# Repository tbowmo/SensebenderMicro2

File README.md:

## Sensebender Micro v2

Revamped Sensebender Micro, with Atmel SAMD20 processor instead of atmega 328p.

Enhancements over old Sensebender:

- up to 256Kb flash/32Kb RAM for code
- up to 48Mhz operating freq.
- 2 LEDs
- Dual radio
  - RFM69
  - NRF24 mini / smd
- onboard voltage regulator, can be disabled / bypassed with solderbridges
- Temperature / Humidity sensor Si7021
- Onboard external flash for future OTA (bootloader is not developed yet)
- Use [MYSX2.4](https://www.mysensors.org/hardware/mysx#mysx-24) connector for add-on boards

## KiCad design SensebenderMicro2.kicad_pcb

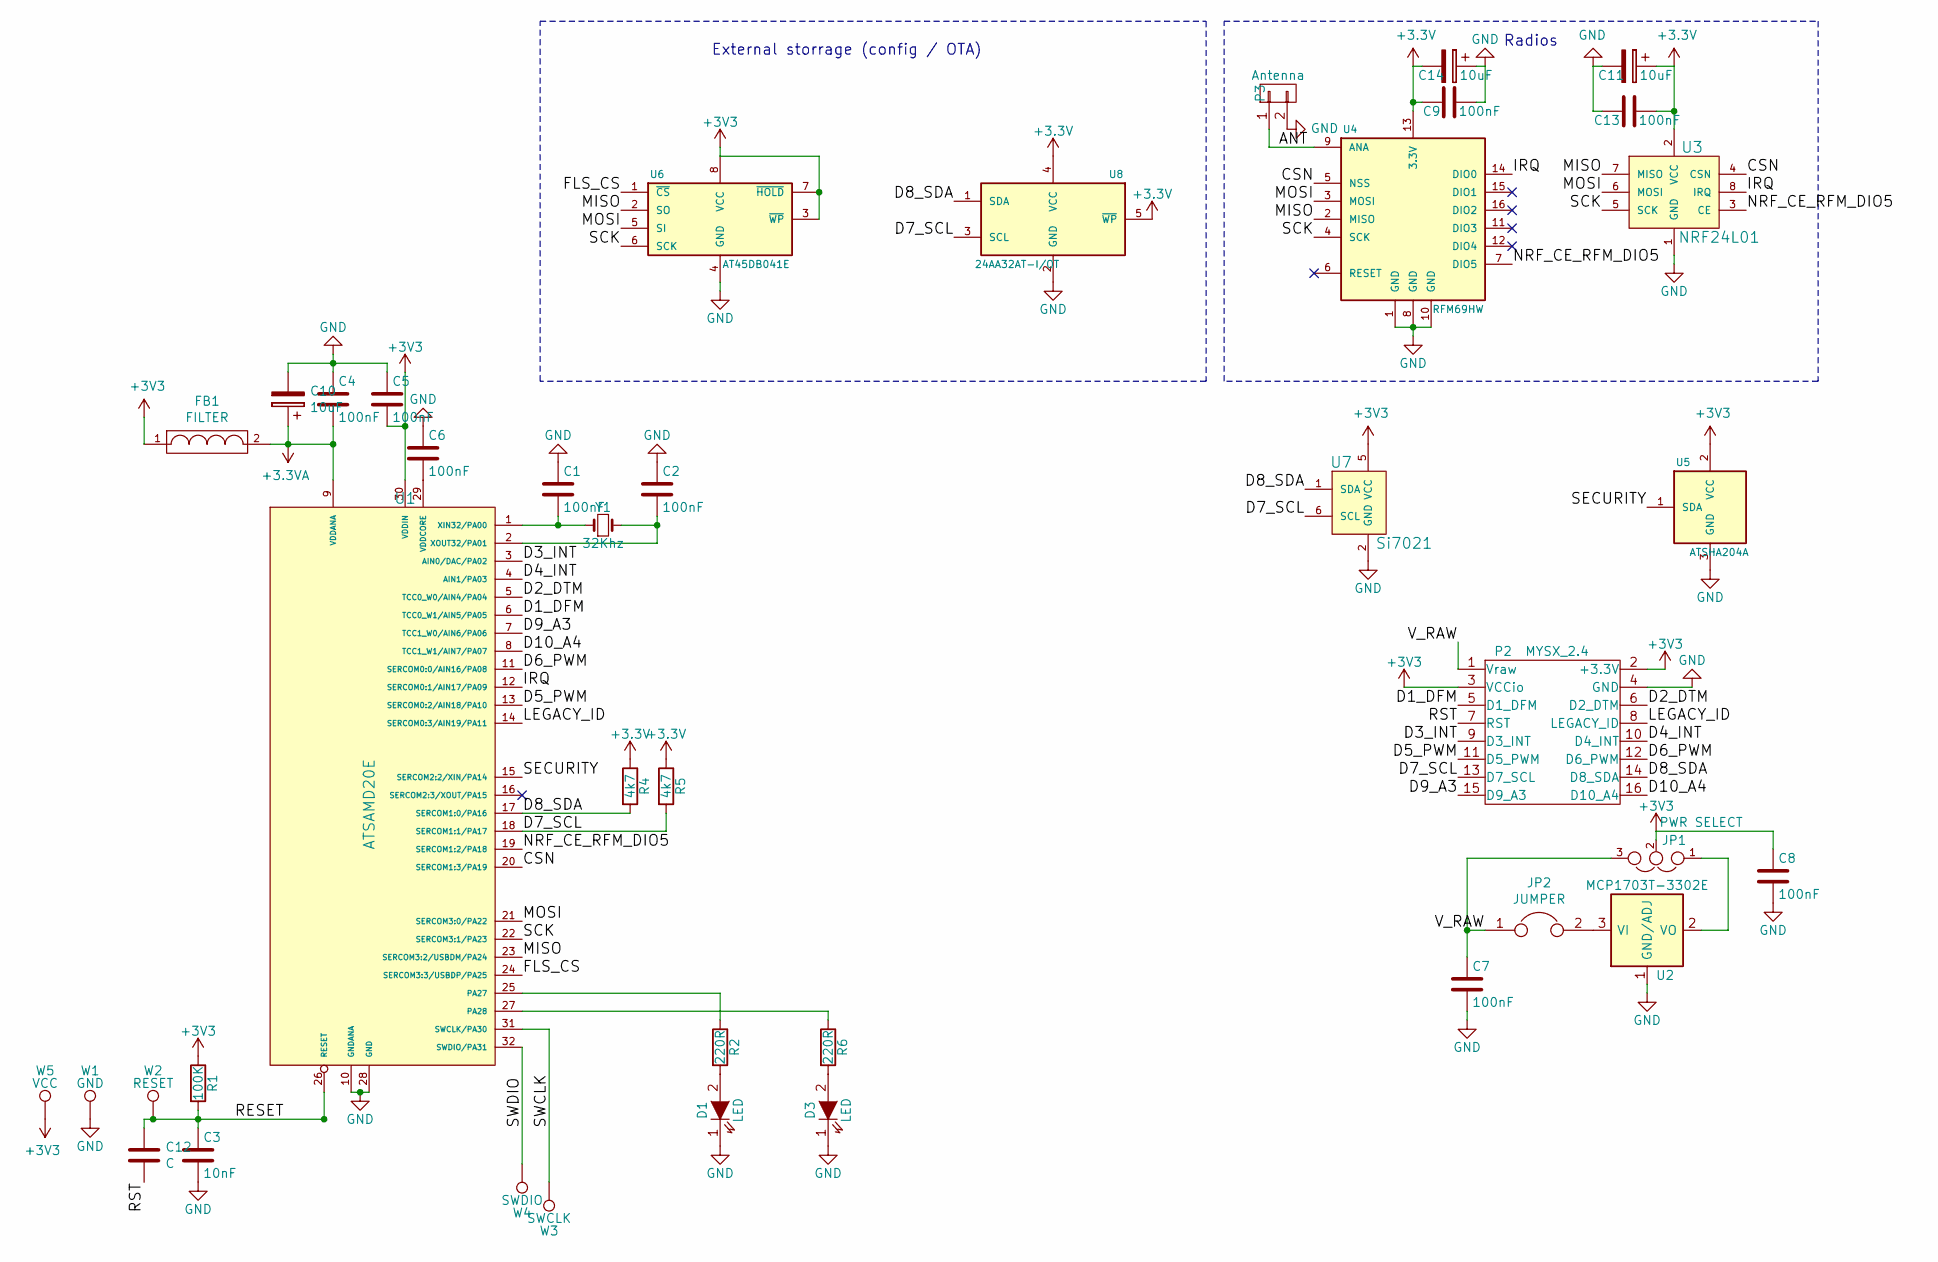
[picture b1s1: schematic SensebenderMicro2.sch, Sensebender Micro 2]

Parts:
C1, C2, C4, C5, C6, C7, C8, C9, C13: 100nF; C_0603
C3: 10nF; C_0603
C10, C11, C14: 10uF; C_0603
C12: C; C_0603
D1, D3: LED; LED-0603
FB1: FILTER; R_0603
JP1: PWR SELECT; 3_pin_solder_jumper_smd
JP2: JUMPER; 2_pin_solder_jumper_smd
P2: MYSX_2.4; MYSX_1.3
P3: Antenna; Pin_Header_Angled_1x02
R1: 100K; R_0603
R2, R6: 220R; R_0603
R4, R5: 4k7; R_0603
U1: ATSAMD20E; TQFP-32_7x7mm_Pitch0.8mm
U2: MCP1703T-3302E; SOT-23
U3: NRF24L01; NRF24L01-SMD
U4: RFM69HW; RFM69HW_SMD_Handsoldering
U5: ATSHA204A; SOT-23_Handsoldering
U6: AT45DB041E; SOIC-8_3.9x4.9mm_Pitch1.27mm
U7: Si7021; DFN-6-1EP_3x3mm_Pitch0.95mm
U8: 24AA32AT-I/OT; SOT-23-5
W1: GND; Measurement_Point_Round-SMD-Pad_Small
W2: RESET; Measurement_Point_Round-SMD-Pad_Small
W3: SWCLK; Measurement_Point_Round-SMD-Pad_Small
W4: SWDIO; Measurement_Point_Round-SMD-Pad_Small
W5: VCC; Measurement_Point_Round-SMD-Pad_Small
Y1: 32Khz; XTAL_3.2x1.5mm

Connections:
+3.3VA: C4.2, C10.1, FB1.2, U1.9 (VDDANA)
/ANT: P3.1, U4.9 (ANA)
/CSN: U1.20 (SERCOM1:3/PA19), U3.4 (CSN), U4.5 (NSS)
/D1_DFM: P2.5 (D1_DFM), U1.6 (TCC0_W1/AIN5/PA05)
/D2_DTM: P2.6 (D2_DTM), U1.5 (TCC0_W0/AIN4/PA04)
/D3_INT: P2.9 (D3_INT), U1.3 (AIN0/DAC/PA02)
/D4_INT: P2.10 (D4_INT), U1.4 (AIN1/PA03)
/D5_PWM: P2.11 (D5_PWM), U1.13 (SERCOM0:2/AIN18/PA10)
/D6_PWM: P2.12 (D6_PWM), U1.11 (SERCOM0:0/AIN16/PA08)
/D7_SCL: P2.13 (D7_SCL), R5.2, U1.18 (SERCOM1:1/PA17), U7.6 (SCL), U8.3 (SCL)
/D8_SDA: P2.14 (D8_SDA), R4.2, U1.17 (SERCOM1:0/PA16), U7.1 (SDA), U8.1 (SDA)
/D9_A3: P2.15 (D9_A3), U1.7 (TCC1_W0/AIN6/PA06)
/D10_A4: P2.16 (D10_A4), U1.8 (TCC1_W1/AIN7/PA07)
/FLS_CS: U1.24 (SERCOM3:3/USBDP/PA25), U6.1 (~CS)
/IRQ: U1.12 (SERCOM0:1/AIN17/PA09), U3.8 (IRQ), U4.14 (DIO0)
/LEGACY_ID: P2.8 (LEGACY_ID), U1.14 (SERCOM0:3/AIN19/PA11)
/MISO: U1.23 (SERCOM3:2/USBDM/PA24), U3.7 (MISO), U4.2 (MISO), U6.2 (SO)
/MOSI: U1.21 (SERCOM3:0/PA22), U3.6 (MOSI), U4.3 (MOSI), U6.5 (SI)
/NRF_CE_RFM_DIO5: U1.19 (SERCOM1:2/PA18), U3.3 (CE), U4.7 (DIO5)
/RESET: C3.1, C12.1, R1.2, U1.26 (RESET), W2.1
/RST: C12.2, P2.7 (RST)
/SCK: U1.22 (SERCOM3:1/PA23), U3.5 (SCK), U4.4 (SCK), U6.6 (SCK)
/SECURITY: U1.15 (SERCOM2:2/XIN/PA14), U5.1 (SDA)
/SWCLK: U1.31 (SWCLK/PA30), W3.1
/SWDIO: U1.32 (SWDIO/PA31), W4.1
/V_RAW: C7.1, JP1.3, JP2.1, P2.1 (Vraw)
GND: C1.1, C2.1, C3.2, C4.1, C5.1, C6.1, C7.2, C8.2, C9.1, C10.2, C11.2, C13.2, C14.1, D1.1 (K), D3.1 (K), P2.4 (GND), P3.2, U1.10 (GNDANA), U1.28 (GND), U2.1 (GND/ADJ), U3.1 (GND), U4.1 (GND), U4.8 (GND), U4.10 (GND), U5.3 (GND), U6.4 (GND), U7.2 (GND), U8.2 (GND), W1.1
unnamed: C1.2, U1.1 (XIN32/PA00), Y1.1
unnamed: C2.2, U1.2 (XOUT32/PA01), Y1.2
unnamed: C6.2, U1.29 (VDDCORE)
unnamed: D1.2 (A), R2.2
unnamed: D3.2 (A), R6.2
unnamed: JP1.1, U2.2 (VO)
unnamed: JP2.2, U2.3 (VI)
unnamed: R2.1, U1.25 (PA27)
unnamed: R6.1, U1.27 (PA28)

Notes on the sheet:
Radios
External storrage (config / OTA)

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
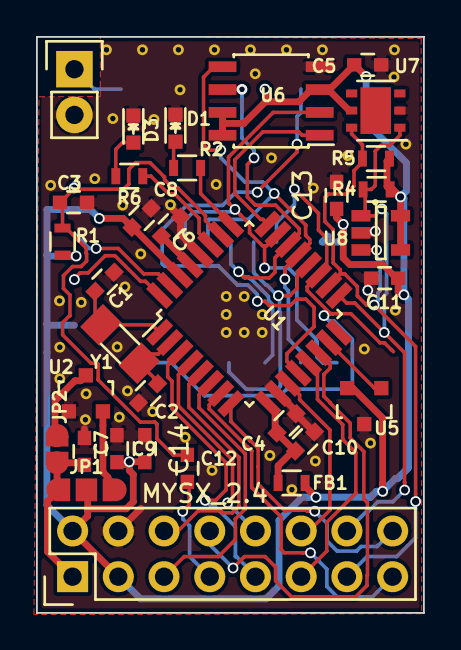
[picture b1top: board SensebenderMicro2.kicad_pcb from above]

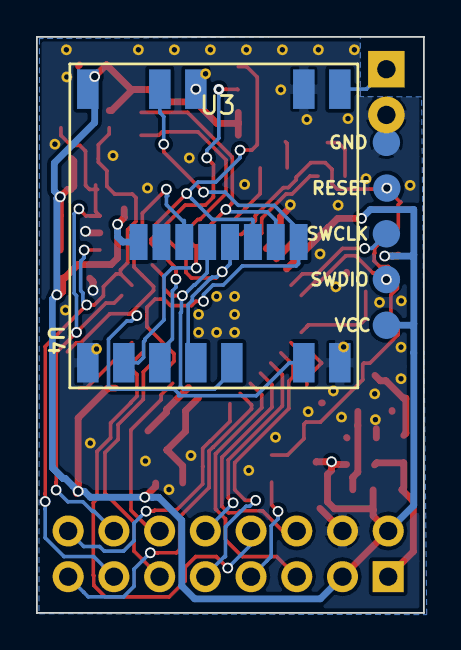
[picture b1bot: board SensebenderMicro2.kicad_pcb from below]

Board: 2 copper layers, 21.5 x 32.0 mm, 40 parts (7 on the bottom side), 37 nets.

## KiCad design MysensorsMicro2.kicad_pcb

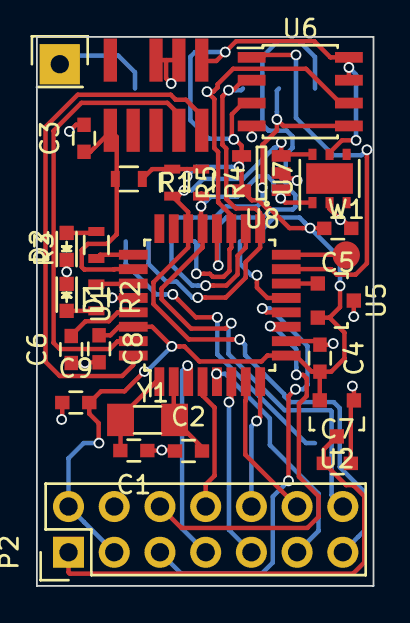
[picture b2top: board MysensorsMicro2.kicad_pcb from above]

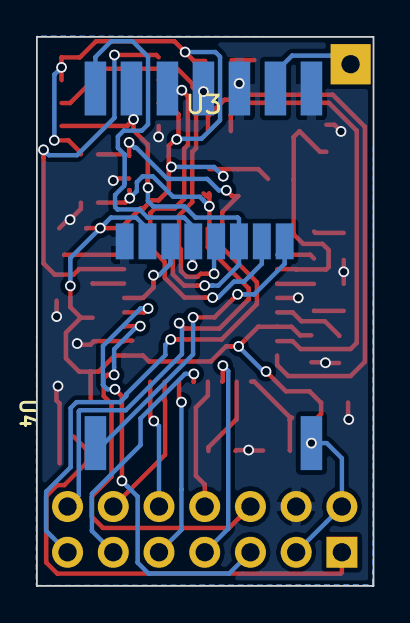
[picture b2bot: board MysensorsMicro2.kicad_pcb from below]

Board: 2 copper layers, 18.7 x 30.5 mm, 29 parts (2 on the bottom side), 33 nets.

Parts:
C1, C2, C4, C5, C6, C7, C8, C9: C; C_0603
C3: 10nF; C_0603
D1, D2: LED; LED-0603
P1: Debug; Cortex_M_Debug_Connector
P2: MYSX_1.2; MYSX_1.3
P3: Antenna; Pin_Header_Straight_1x01
R1: 100K; R_0603
R2, R3: R; R_0603
R4, R5: 4k7; R_0603
U1: ATSAMD21E; TQFP-32_7x7mm_Pitch0.8mm
U2: AP1117D33; SOT-23
U3: NRF24L01; NRF24L01-SMD
U4: RFM69HW; RFM69HW_SMD_Handsoldering
U5: ATSHA204A; SOT-23
U6: AT25DF512C; SOIC-8_3.9x4.9mm_Pitch1.27mm
U7: Si7021; DFN-6-1EP_3x3mm_Pitch0.95mm
U8: AT24C32-STUM-T; SOT-23-5
W1: TEST_1P; Measurement_Point_Round-SMD-Pad_Small
Y1: 32Khz; XTAL_3.2x1.5mm

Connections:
+3V3: C4.2, C5.2, C8.1, C9.2, P1.1, P2.2, P2.3, R1.1, R4.1, R5.1, U1.9, U1.30, U2.2, U3.2, U4.8, U5.2, U6.3, U6.7, U6.8, U7.5, U8.4, U8.5
/A1: P2.7, U1.3
/A2: P2.8, U1.4
/BOOTMODE: U1.16, W1.1
/CSN: U1.20, U3.4, U4.15
/D1_DFM: P2.5, U1.12
/D2_DTM: P2.6, U1.11
/D3_INT: P2.9, U1.6
/D4_INT: P2.10, U1.8
/D5_PWM: P2.11, U1.5
/D6_PWM: P2.12, U1.7
/D7_SCL: P2.13, R5.2, U1.22, U7.6, U8.3
/D8_SDA: P2.14, R4.2, U1.21, U7.1, U8.1
/FLS_CS: U1.15, U6.1
/IRQ: U3.8, U4.2
/MISO: U1.17, U3.7, U4.13, U6.2
/MOSI: U1.18, U3.6, U4.14, U6.5
/NRF_CE: U1.13, U3.3
/RESET: C3.1, P1.10, R1.2, U1.26
/SCK: U1.19, U3.5, U4.12, U6.6
/SECURITY: U1.14, U5.1
/SWCLK: P1.4, U1.31
/SWDIO: P1.2, U1.32
/V_RAW: C7.1, P2.1, U2.3
GND: C1.1, C2.1, C3.2, C4.1, C5.1, C6.1, C7.2, C8.2, C9.1, D1.1, D2.1, P1.3, P1.5, P2.4, U1.10, U1.28, U2.1, U3.1, U4.9, U4.11, U5.3, U6.4, U7.2, U8.2
unnamed: C1.2, U1.1, Y1.1
unnamed: C2.2, U1.2, Y1.2
unnamed: C6.2, U1.29
unnamed: D1.2, R2.2
unnamed: D2.2, R3.2
unnamed: P3.1, U4.10
unnamed: R2.1, U1.27
unnamed: R3.1, U1.25

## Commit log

2016-02-12 Adding CERN files
2016-02-12 Brought in prepare.sh from nrf2rfm module
2016-02-12 Added testpads to reset signal + gnd
2016-02-13 Renamed to SensebenderMicro2
2016-03-16 Added filtering for analog supply
2016-03-16 Added readme file
2016-03-16 Updated README file
2016-05-01 Added fet to switch power to radio / ATSHA
2016-05-02 Added Gate pull up and series resistor to Q1
2016-05-02 Rerouted to make room for GND via at C7
2016-07-13 added reset / DIO5 connections to RFM69
2016-11-16 Updated to use MYSX2.x with reset
    Also shuffled peripherals around on the samd, to make routing easier
2016-11-16 Added pin analysis spreadsheet
2016-11-16 Updated manufacturing preview files
2016-11-18 updated silkscreen placements
2016-11-20 recreated routing with better ground plane
2016-11-24 Updated routing, waveguide for rfm69
2016-11-27 Updated routing, gnd on component side
2017-02-07 Updates to layout, copper pour etc
2017-02-07 Added extra 10uF caps to radios
2017-02-22 Updated gerbers, preparing for pcb ordering
2017-05-27 Updated vendor references
2017-05-27 Added BOM file
2017-07-05 Changed to use RFM69HCW footprint (compatible with RFM95)
2017-07-16 Updated layout a bit
